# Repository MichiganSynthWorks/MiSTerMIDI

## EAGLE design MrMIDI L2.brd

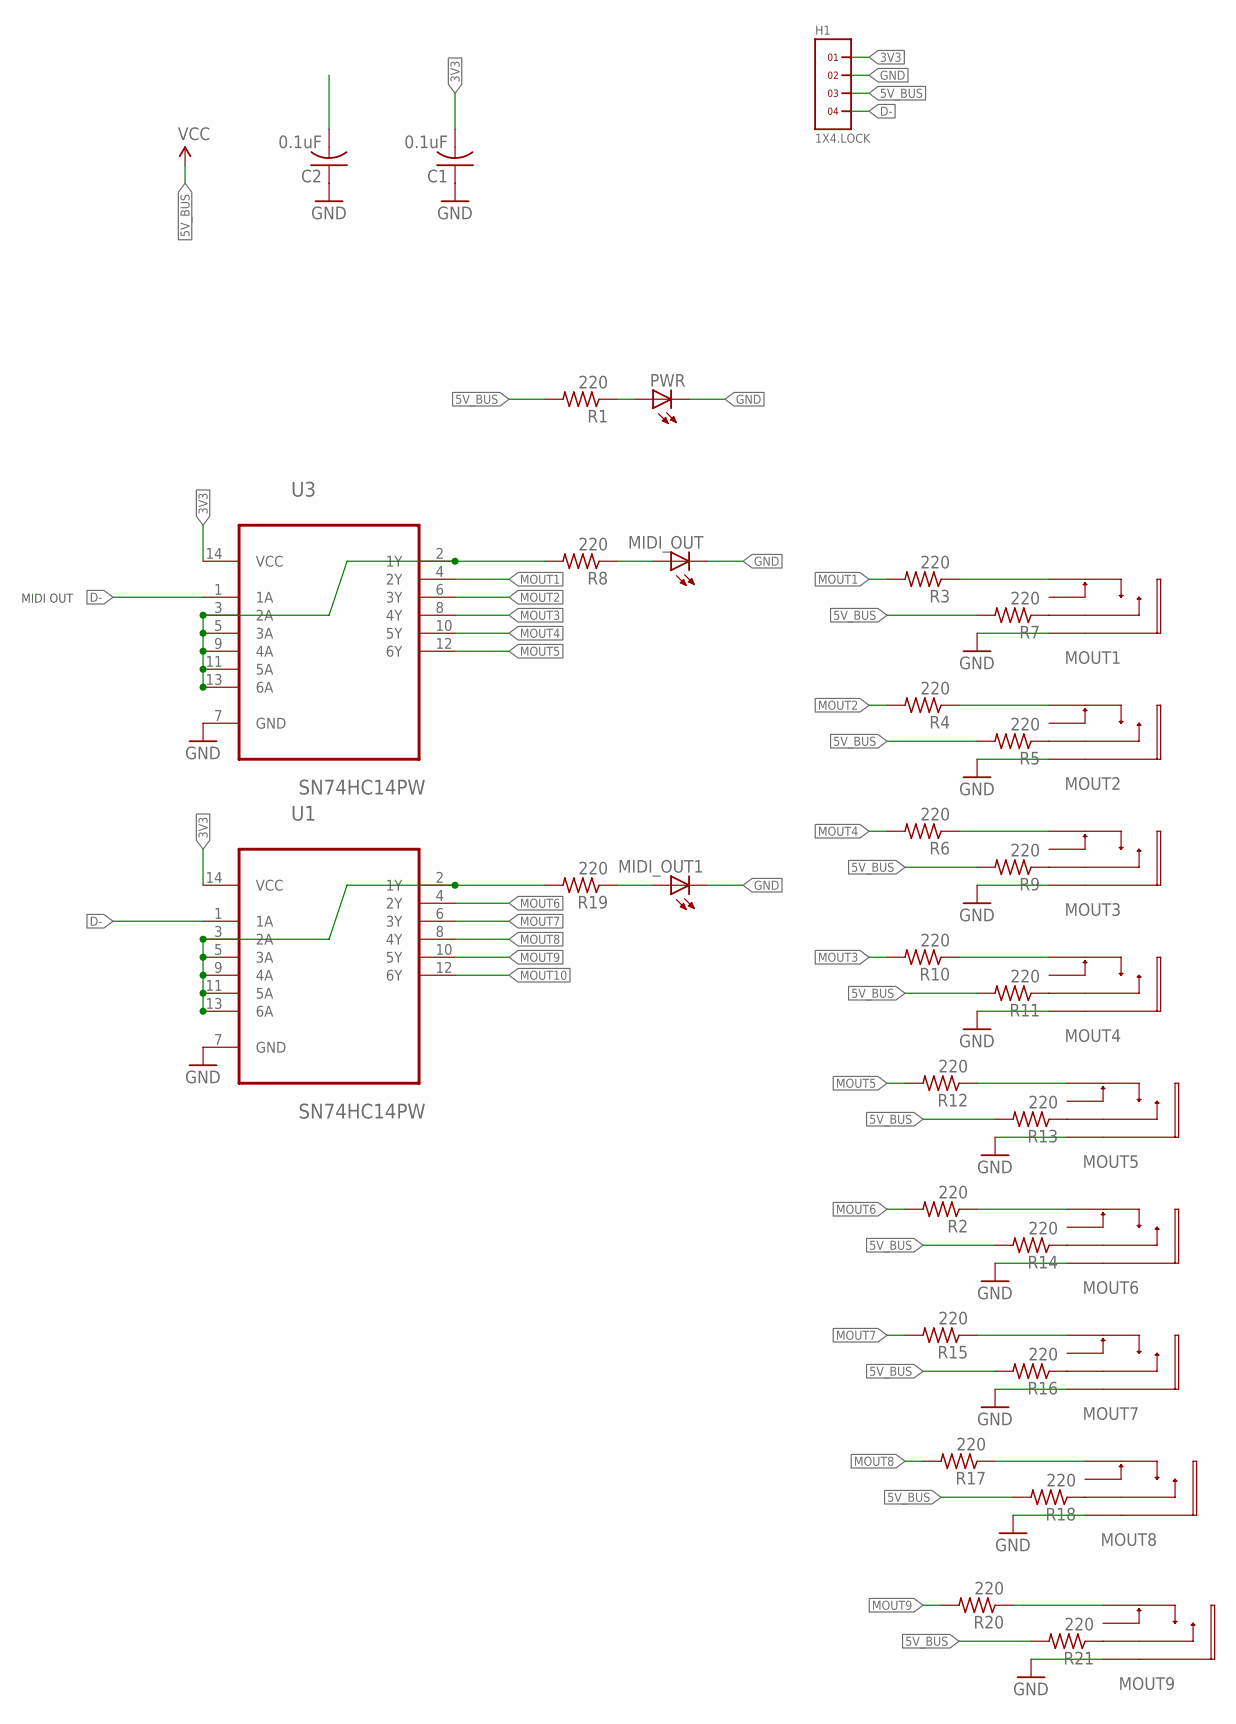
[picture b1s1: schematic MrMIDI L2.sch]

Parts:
C1, C2: 0.1uF; RCL_C0603K
H1: 1X4.LOCK
MIDI_OUT, MIDI_OUT1: LEDCHIPLED_0603; CHIPLED_0603
MOUT1, MOUT2, MOUT3, MOUT4, MOUT5, MOUT6, MOUT7, MOUT8, MOUT9: PJ327E; PJ327
PWR: LEDCHIPLED_0603; CHIPLED_0603
R1, R2, R3, R4, R5, R6, R7, R8, R9, R10, R11, R12, R13, R14, R15, R16, R17, R18, R19, R20, R21: 220; RCL_R0402
U1, U3: SN74HC14PW; SOP65P640X120-14N

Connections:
3V3: C1.2, H1.1, U1.14 (VCC), U3.14 (VCC)
5V_BUS: C2.2, H1.3, R1.2, R5.2, R7.2, R9.2, R11.2, R13.2, R14.2, R16.2, R18.2, R21.2
D-: H1.4, U1.1 (1A), U3.1 (1A)
GND: C1.1, C2.1, H1.2, MIDI_OUT.C, MIDI_OUT1.C, MOUT1.P$1, MOUT1.P$4, MOUT2.P$1, MOUT2.P$4, MOUT3.P$1, MOUT3.P$4, MOUT4.P$1, MOUT4.P$4, MOUT5.P$1, MOUT5.P$4, MOUT6.P$1, MOUT6.P$4, MOUT7.P$1, MOUT7.P$4, MOUT8.P$1, MOUT8.P$4, MOUT9.P$1, MOUT9.P$4, PWR.C, U1.7 (GND), U3.7 (GND)
MOUT1: R3.2, U3.4 (2Y)
MOUT2: R4.2, U3.6 (3Y)
MOUT3: R10.2, U3.8 (4Y)
MOUT4: R6.2, U3.10 (5Y)
MOUT5: R12.2, U3.12 (6Y)
MOUT6: R2.2, U1.4 (2Y)
MOUT7: R15.2, U1.6 (3Y)
MOUT8: R17.2, U1.8 (4Y)
MOUT9: R20.2, U1.10 (5Y)
MOUT10: U1.12 (6Y)
unnamed: MIDI_OUT.A, R8.1
unnamed: MOUT5.P$3, R13.1
unnamed: MOUT6.P$3, R14.1
unnamed: R8.2, U3.2 (1Y), U3.3 (2A), U3.5 (3A), U3.9 (4A), U3.11 (5A), U3.13 (6A)
unnamed: MOUT1.P$3, R7.1
unnamed: MOUT1.P$2, R3.1
unnamed: MOUT2.P$3, R5.1
unnamed: MOUT2.P$2, R4.1
unnamed: MOUT3.P$3, R9.1
unnamed: MOUT3.P$2, R6.1
unnamed: MOUT4.P$3, R11.1
unnamed: MOUT4.P$2, R10.1
unnamed: MOUT6.P$2, R2.1
unnamed: MOUT5.P$2, R12.1
unnamed: MOUT7.P$3, R16.1
unnamed: MOUT7.P$2, R15.1
unnamed: PWR.A, R1.1
unnamed: MOUT8.P$3, R18.1
unnamed: MOUT8.P$2, R17.1
unnamed: R19.2, U1.2 (1Y), U1.3 (2A), U1.5 (3A), U1.9 (4A), U1.11 (5A), U1.13 (6A)
unnamed: MIDI_OUT1.A, R19.1
unnamed: MOUT9.P$3, R21.1
unnamed: MOUT9.P$2, R20.1

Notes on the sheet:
MIDI OUT

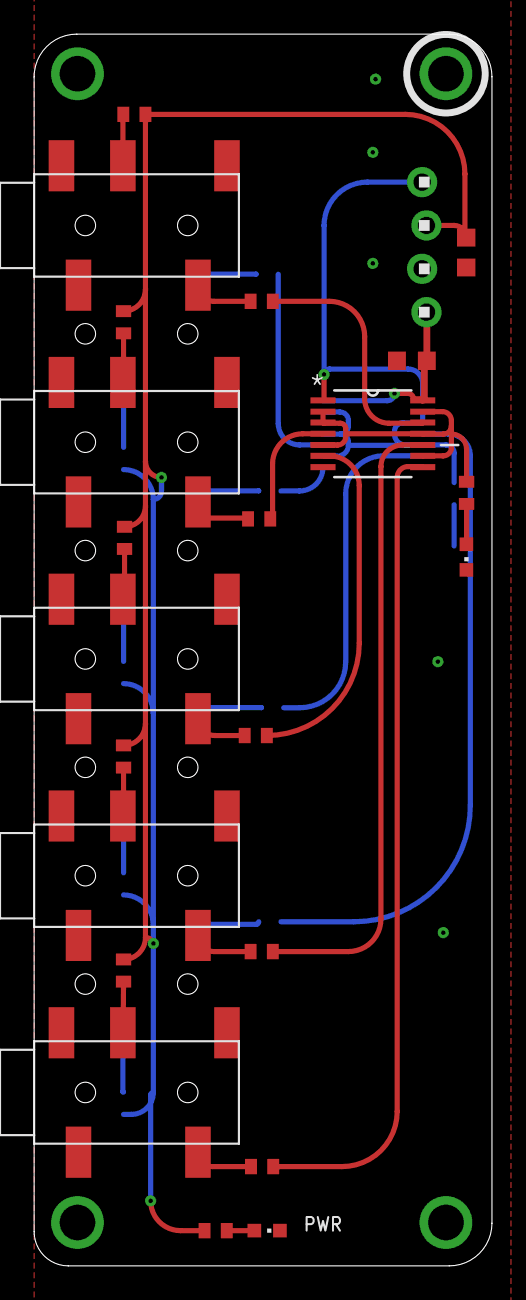
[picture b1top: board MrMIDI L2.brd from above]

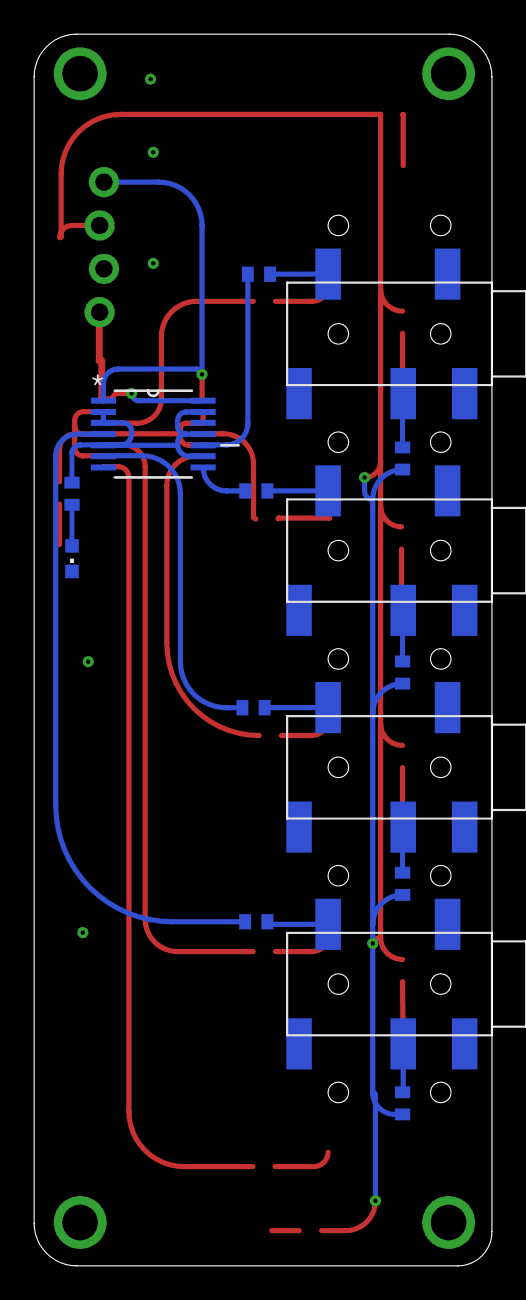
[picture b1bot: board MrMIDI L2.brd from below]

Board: 2 copper layers, 26.8 x 72.2 mm, 39 parts (15 on the bottom side), 36 nets.

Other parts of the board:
U$1: MSW_LOGO_0.5"

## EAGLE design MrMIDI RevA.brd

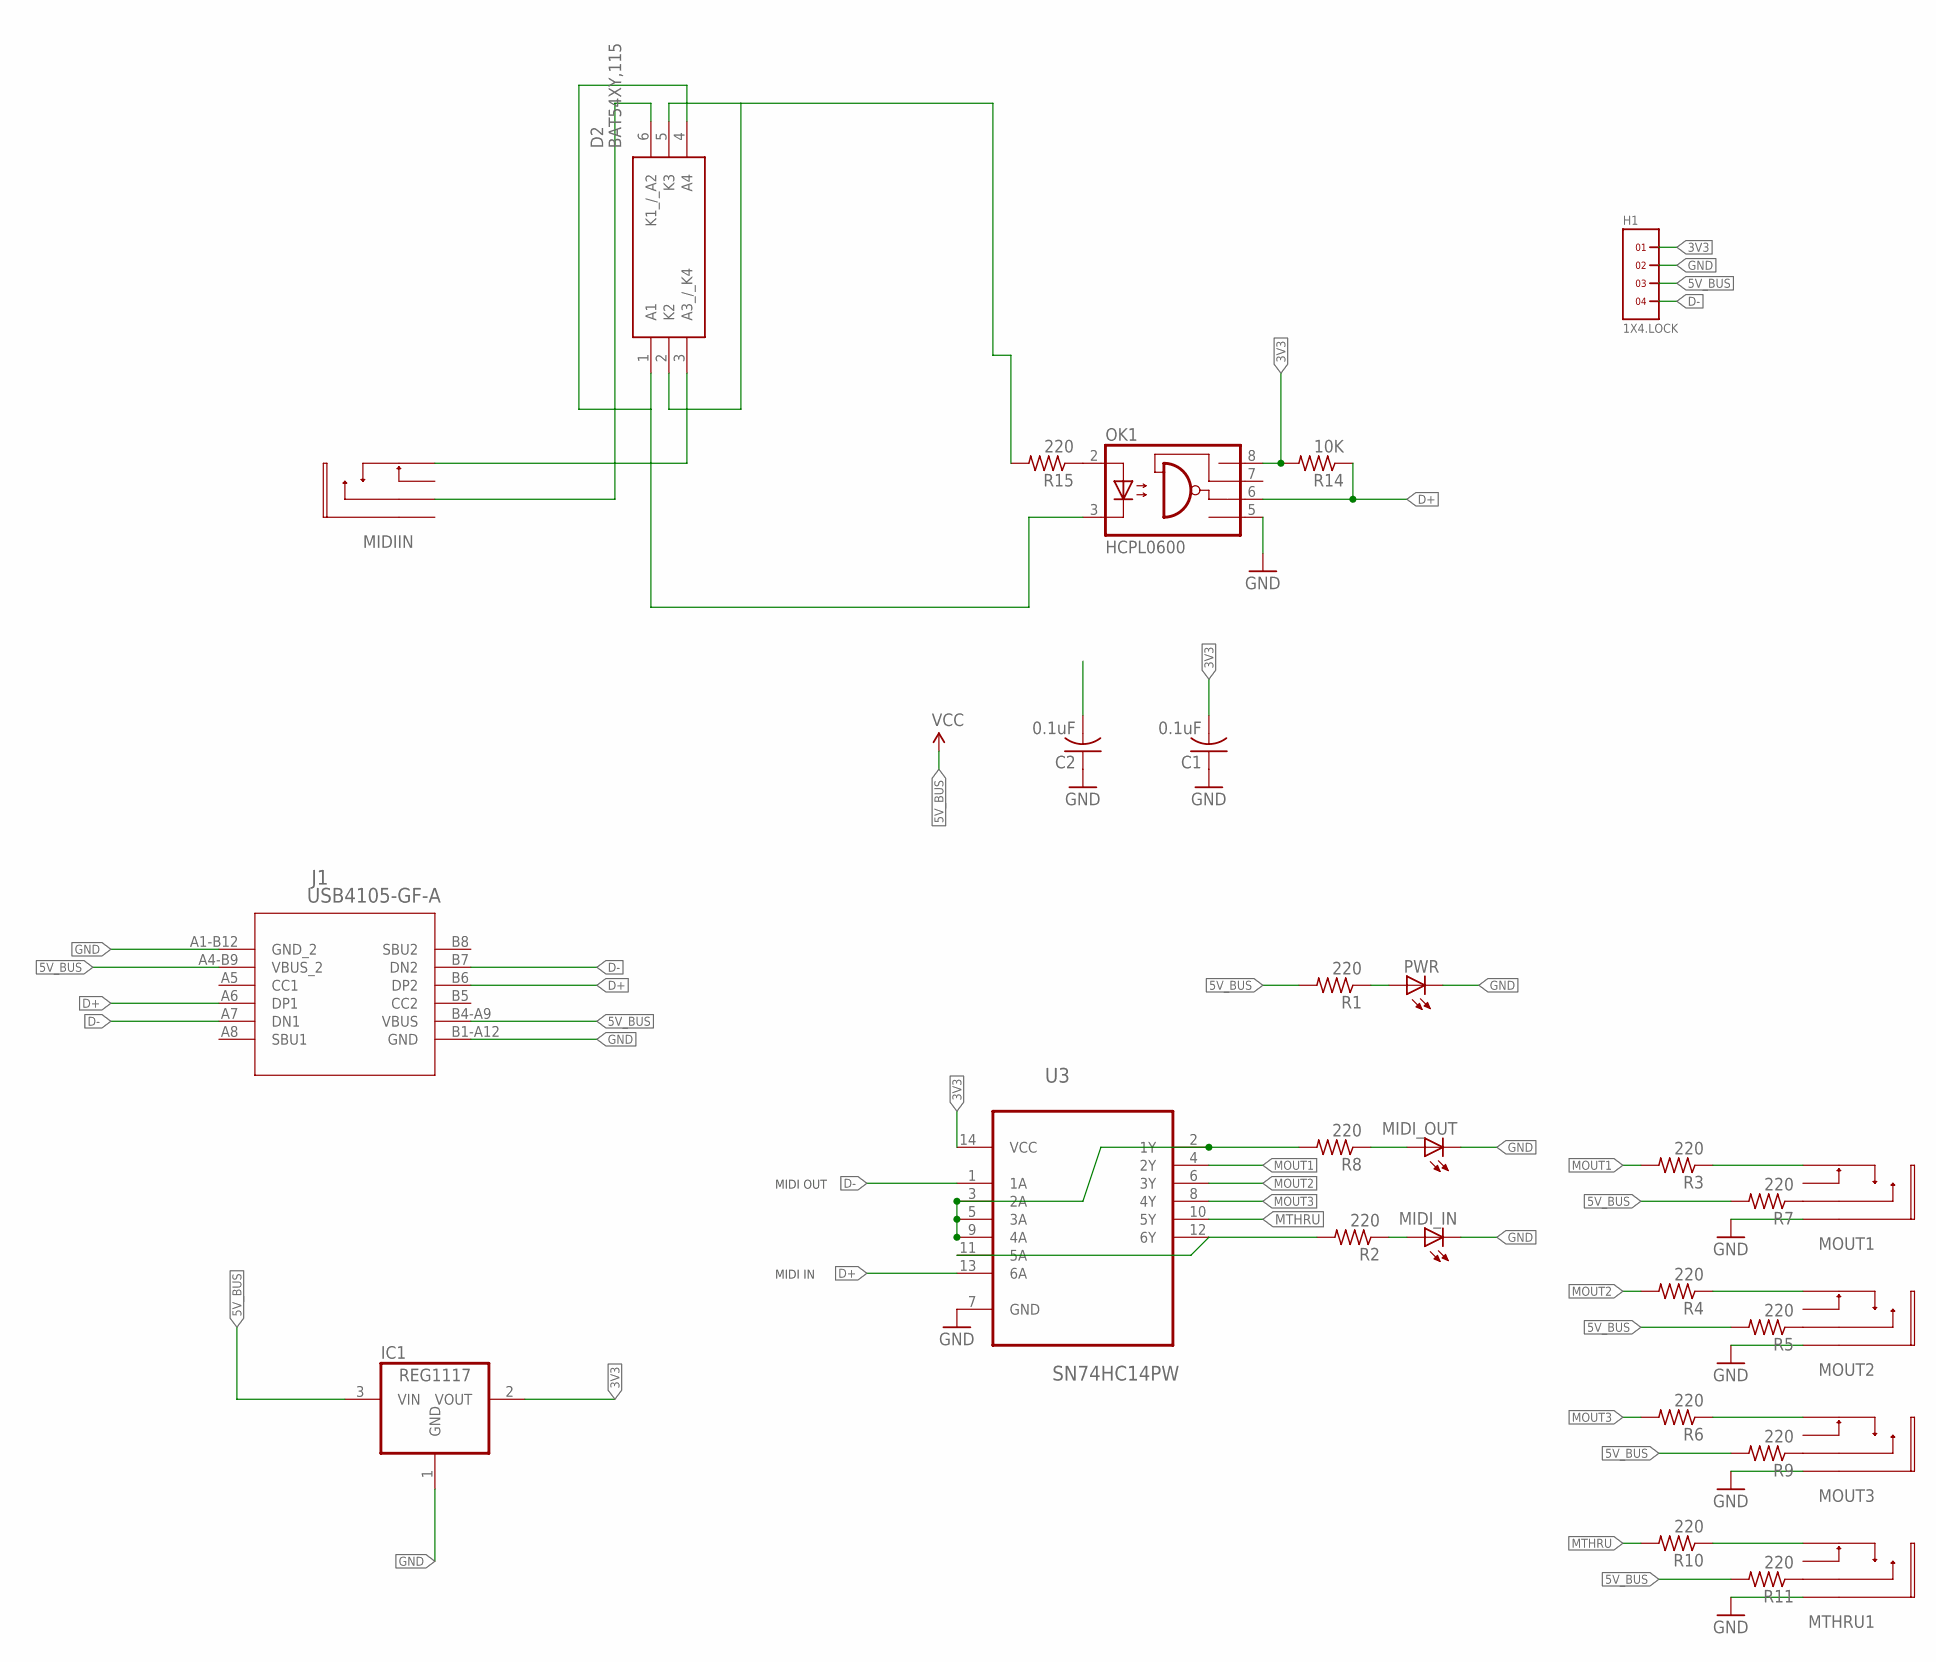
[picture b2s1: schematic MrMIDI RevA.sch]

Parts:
C1, C2: 0.1uF; RCL_C0603K
D2: BAT54XY,115; SOT65P210X110-6N
H1: 1X4.LOCK
IC1: REG1117; SOT223
J1: USB4105-GF-A; USB4105_GCT
MIDIIN: PJ327E; PJ327
MIDI_IN: LEDCHIPLED_0603; CHIPLED_0603
MIDI_OUT: LEDCHIPLED_0603; CHIPLED_0603
MOUT1, MOUT2, MOUT3: PJ327E; PJ327
MTHRU1: PJ327E; PJ327
OK1: HCPL0600; SOIC08
PWR: LEDCHIPLED_0603; CHIPLED_0603
R1, R2, R3, R4, R5, R6, R7, R8, R9, R10, R11, R15: 220; RCL_R0402
R14: 10K; RCL_R0402
U3: SN74HC14PW; SOP65P640X120-14N

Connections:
3V3: C1.2, H1.1, IC1.2 (VOUT), OK1.8 (VCC), R14.2, U3.14 (VCC)
5V_BUS: C2.2, H1.3, IC1.3 (VIN), J1.A4-B9 (VBUS_2), J1.B4-A9 (VBUS), R1.2, R5.2, R7.2, R9.2, R11.2
D+: J1.A6 (DP1), J1.B6 (DP2), OK1.6 (VO), R14.1, U3.13 (6A)
D-: H1.4, J1.A7 (DN1), J1.B7 (DN2), U3.1 (1A)
GND: C1.1, C2.1, H1.2, IC1.1 (GND), J1.A1-B12 (GND_2), J1.B1-A12 (GND), MIDI_IN.C, MIDI_OUT.C, MOUT1.P$1, MOUT1.P$4, MOUT2.P$1, MOUT2.P$4, MOUT3.P$1, MOUT3.P$4, MTHRU1.P$1, MTHRU1.P$4, OK1.5 (GND), PWR.C, U3.7 (GND)
MIDI_IN_RING: D2.6 (K1_/_A2), MIDIIN.P$3
MIDI_IN_TIP: D2.3 (A3_/_K4), MIDIIN.P$2
MOUT1: R3.2, U3.4 (2Y)
MOUT2: R4.2, U3.6 (3Y)
MOUT3: R6.2, U3.8 (4Y)
MTHRU: R10.2, U3.10 (5Y)
unnamed: MIDI_OUT.A, R8.1
unnamed: D2.1 (A1), D2.4 (A4), OK1.3 (C)
unnamed: R2.2, U3.11 (5A), U3.12 (6Y)
unnamed: R8.2, U3.2 (1Y), U3.3 (2A), U3.5 (3A), U3.9 (4A)
unnamed: MOUT1.P$3, R7.1
unnamed: MOUT1.P$2, R3.1
unnamed: MOUT2.P$3, R5.1
unnamed: MOUT2.P$2, R4.1
unnamed: MOUT3.P$3, R9.1
unnamed: MOUT3.P$2, R6.1
unnamed: MTHRU1.P$3, R11.1
unnamed: MTHRU1.P$2, R10.1
unnamed: MIDI_IN.A, R2.1
unnamed: OK1.2 (A), R15.1
unnamed: D2.2 (K2), D2.5 (K3), R15.2
unnamed: PWR.A, R1.1

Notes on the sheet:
MIDI OUT
MIDI IN

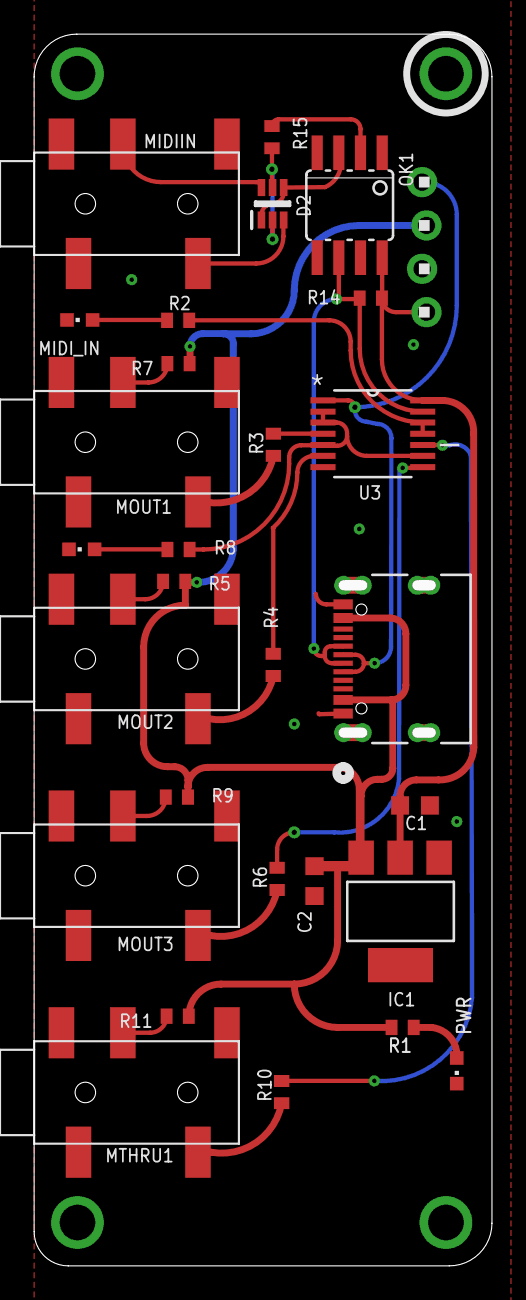
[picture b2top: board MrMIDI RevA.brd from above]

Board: 2 copper layers, 26.2 x 71.6 mm, 30 parts (0 on the bottom side), 27 nets.

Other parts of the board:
U$1: MSW_LOGO_0.5"

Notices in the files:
parts and their libraries:
COPYRIGHT: Copyright (C) 2022 Ultra Librarian. All rights reserved.
